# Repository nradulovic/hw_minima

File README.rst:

.. contents:: Table of Contents
   :depth: 3

Introduction
============

This document shall describe rationales used to design and build audio 
power amplifier using LM1875 integrated circuit.

Architecture
============

The amplifier architecture consists of the following sections:

* Input circuit
* Power amplifier
* Power supply

All sections are located on separate PCB boards.

.. image:: images/pcb_from_top.png

.. image:: images/pcb_render_corner.png

.. image:: images/pcb_render_from_top.png

Input circuit 
==================================

The input circuit contains:

* Input EMI suppression

Input EMI suppression
---------------------

To protect the input from EMI we will use the following Zobel network:

.. code::
          o Positive input or negative input
          |
          |
        ----- Czi
        -----
          |
          |
         +-+  Rzi
         | |
         | |
         +-+
          |
         === Ground

For most input cables characteristic impedance falls in range between
50 and 100ohm impedance and we are using the 75ohm as the middle value. The
resistor Rzi is ``Rzi=75ohm`` and the capacitor Czi is ``Czi=220pF``.
This network should be placed right at the input connector, not on the
main amplifier PCB.

Also, a 100n X7R capacitor shall be placed between SGND and chassis right at the
input connector. This capacitor will shunt radio and other interfirence signal
into the Chassis Ground potential.

Power amplifier
===============

* Input low pass filter
* The ground loop breaker resistor
* Output EMI suppression

Input low pass filter
---------------------

For input filter we choose the frequency between 300kHz and 400kHz.

.. code::

        +---+ Rlp1    +---+ Rlp2
    0---+   +----+----+   +---+---o Toward Amplifier IC block
        +---+    |    +---+   |
               ----- Clp1   ----- Clp2
               -----        -----
                 |            |
                === Ground   === Ground

Using the 2nd order CR low-pass filter calculator at URL:
*http://sim.okawa-denshi.jp/en/CRCRtool.php* we arrive at:

.. math::

    Rlp1 = 100 Ohm, Rlp2 = 100 Ohm

    Clp1 = 220pF,   Clp2 = 2.2nF

    fp1 = 352kHz

    fp2 = 14MHz

For more details please refer to: http://www.johnhearfield.com/RC/RC4.htm

The ground loop breaker resistor
--------------------------------

A ground loop breaker resistor is located between SGND and GNDPWR grounds. The
value of this resistor should be around 10 ohms.

Output EMI suppression
----------------------

Output network consists of upstream and downstream Zobel Network and of output
coil (``Ld``) with parallel, damping resistor (``Rd``). Upstream Zobel network 
provides a low-inductance load for the output stage at very high frequencies 
and allows high-frequency currents to circulate local to the output stage. The 
downstream Zobel network provides a good resistive termination right at the 
speaker terminals at high frequencies, helping to reduce RFI ingress and damp
resonances with, or reflections from, the speaker cables.
The output circuit is the following:

.. code::

    Ld
             xxx
        +---x   x   x---+
        |        xxx    |
        |               |
        |   +-------+   |
    o---+---|       |---+---o
    Vout    +-------+   |   Vspeaker
        Rd              |
                      ----- Cz2 = 100nF
                      -----
                        |
                        |
                       +-+  Rz1 = 10 Ohm
                       | |
                       | |
                       +-+
                        |
                       ===

The output coil ``Ld`` provides high frequency isolation of output load from 
output stage of LM1875. The inductance value should be between 2uH up to 5uH. 
Output shunt resistor should be between 2 Ohm and 5 Ohms. See 
*Douglas Self - Audio Power Amplifier Design Handbook, 3rd Ed., Output networks, 
chapter 7* for effect on power amplifier transfer function.

Power dissipation
-----------------

**NOTE:**

* Maximum power dissipation should be around 25W per IC package for LM1875.

Fortunately, with music signals the power dissipation should be lower. 
Effective power of music signal is about 2 to 10 times as smaller than 
effective power of sinusoid signal. The power transformer is 200VA, meaning 
that each channel gets 100VA of power. Since the maximum output power at 8ohms 
is approximately 50W we get that the transformer supports crest factor of 4 
(see: 
*https://www.neurochrome.com/taming-the-lm3886-chip-amplifier/power-supply-design*).

Gain value
----------

For this power amplifier we are using non-inverting topology for simplicity
reasons. If you would like to have less distortion then LM1875 should be used
in inverting configuration.

The equivalent gain circuit resistance needs to stay below 600ohms. This is so
because all noise measurements in data-sheet were done with 600ohms or 0ohms.

Using low feedback gain is preferred for several reasons:

* there is more loop gain available to reduce the distortion
* reduced output noise
* lower offset at output

Nominal gain is:

.. math::

    G=-Rf/Rg+1

Using E24 series of resistors:

+-----------+-----------+---------+
| Rf [Ohm]  | Rg [kOhm] | G [V/V] |
+-----------+-----------+---------+
| 510       |  7.5      | 15.7    |
+-----------+-----------+---------+
| *510*     |  *8.2*    | *17.0*  |
+-----------+-----------+---------+
| 510       |  9.1      | 18.8    |
+-----------+-----------+---------+
| 510       | 10.0      | 20.6    |
+-----------+-----------+---------+
| 510       | 11.0      | 22.5    |
+-----------+-----------+---------+

Using E48 series of resistors:

+-----------+-----------+---------+
| Rf [Ohm]  | Rg [kOhm] | G [V/V] |
+-----------+-----------+---------+
| 511       |  7.50     | 15.7    |
+-----------+-----------+---------+
| 511       |  7.87     | 16.4    |
+-----------+-----------+---------+
| *511*     |  *8.25*   | *17.1*  |
+-----------+-----------+---------+
| 511       |  8.66     | 17.9    |
+-----------+-----------+---------+
| 511       |  9.09     | 18.8    |
+-----------+-----------+---------+
| 511       |  9.53     | 19.6    |
+-----------+-----------+---------+
| 511       | 10.00     | 20.6    |
+-----------+-----------+---------+
| 511       | 10.50     | 21.5    |
+-----------+-----------+---------+
| 511       | 11.00     | 22.5    |
+-----------+-----------+---------+
| 499       |  7.50     | 16.0    |
+-----------+-----------+---------+

Chosen values for E24 series:

* Rf = 7.5kOhm
* Rg = 510 Ohm
    
Chosen values for E48 series:

* Rf = 7.5kOhm
* Rg = 499 Ohm
 
Frequency compensation
----------------------

The LM1875 is modeled in the following way:

* ``Aol``, typical open loop gain at DC.
* ``Fp1``, dominant pole.
* ``Fp2``, a pole which probably originates from output stage.
* ``Fp3``, pole which probably originates from input or intermediate stages.
* ``Fp4 Hz``, pole which probably originates from input or intermediate stages.
* ``Rops``, open loop output stage impedance. The OPS open loop impedance is 
  unusually low because the LM1875 uses output inclusive Miller compensation
  which can be observed on the equivalent schematic in the data-sheet.

+-----------+-----------+-----------+-----------+-----------+-----------+-----------+
| Chip      | Aol [dB]  | Fp1 [Hz]  | Fp2 [Hz]  | Fp3 [Hz]  | Fp4 [Hz]  | Rops [Ohm]|
+-----------+-----------+-----------+-----------+-----------+-----------+-----------+
| LM1875    | 90        | 15        | 1.5e6     | 8e6       | 9e6       | 500e-3    |
+-----------+-----------+-----------+-----------+-----------+-----------+-----------+

Lead compensation
`````````````````

Equivalent feedback network with lead compensation circuit::

          + Vout
          |
          *------+
          |      |
         +-+ Rf  |
         | |   ----- Cf=Cl (+Csi, see Input pin capacitance compensation)
         | |   -----
         +-+     |
   Vf     |      |
    +-----*------+
          |
         +-+ Rg
         | |
         | |
         +-+
          |
          + Input

Resistors `Rf` and `Rg` are part of feedback network. Capacitor `Cf` is the
compensation capacitor. The transfer function of this network is given as:

.. math::

    Vf(s)=I(s)*Rg

    Vout(s)=I(s)*(Rf||Cl + Rg)=I(s)*(Rf/(1+s*Rf*Cl)+Rg)

    H(s)=Vf(s)/Vout(s)=(Rg/(Rf+Rg))*((1+s*Rf*Cl)/(1+s*Re*Cl))

Zero: 

.. math::

    wz=1/(Rf*Cl)

Pole: 

.. math::

    wp=1/(Re*Cl)

Where:

.. math::

    Re=Rf||Rg=Rf*Rg/(Rf+Rg)

With this compensation we want to compensate for LM3886 ``fp2`` pole. Although
the ``fp2`` pole has a high value of it still has quite the effect on the gain 
phase near unity gain bandwidth (UGBW) value. To compensate for ``fp2``
pole we can use ``wz`` equation above. 

For LM1875 we would get:

.. math::
    
    Rf = 7.5kOhm
    
    fp2 = 1.5e6 Hz
    
    Cl=1/(2*pi*Rf*fp2)=14.1pF
    
Outcome:

* By using this compensation we improve the loop gain phase around UGBW point
  and at higher frequencies.
* The ``Cf`` in this compensation is known to reduce the closed loop
  bandwidth. Since the ``Cf`` value is so small the impact to closed loop
  bandwidth should be minimal.

Input pin capacitance compensation
``````````````````````````````````

Input pins have the following parasitic capacitances associated:

* Cdiff
* Cm
* Cstray

The LM1875 data-sheet does not specify any parameter regarding parasitic
input capacitances. Voltage feedback OPAMPS usually have both differential and
common-mode input impedances specified. In the absence of any information, it
is safe to use the model given in the next figure:

.. code::

                   +----+ Zdiff
    +input o---+---|    |---+---o -input
               |   +----+   |
               |            |
              +-+ Zcm1     +-+ Zcm2
              | |          | |
              | |          | |
              +-+          +-+
               |            |
              ===          ===

We can use a rough estimation of values based on experience on using other 
audio BJT OPAMPS, and typical values are around ``Cdiff=5pF``, ``Cm=4pF`` 
and ``Cstray=3pF``. All three equivalent capacitors are tied in parallel, 
so the total input capacitance becomes:

.. math::

    Cinput = Cdiff+Cm+Cstray=5pF+5pF+3pF=12pF
    
To mitigate this capacitance we can add capacitance `Csi` parallel to `Rf` 
resistor. To compensate for this the following equation is applied:

.. math::

    Rf*Csi=Rg*Cinput
    
    Csi=Cinput*Rg/Rf=0.8pF
    
Since we are already using lead compensation we just add this value to existing
`Cl` capacitor.

Also, note that LM1875 model has tree more additional poles:

* ``Fp2``, pole which probably originates from input or intermediate 
  stages.
* ``Fp3``, pole which probably originates from input or intermediate 
  stages.
* A pole from ``Rops``, open loop output stage impedance which in conjunction 
  with output Zobel and connected load forms another high frequency pole.
   
Although all above poles are very high in frequency they still have their
impact on lower frequency part of transfer function and reduce a few degrees of
phase margin at UGBW point (approx. at 500kHz). Because of these poles we can
freely put a bit bigger `Cf` capacitor value in the feedback network. Rough
estimation is to put additional 1-3pF.

.. math::

	Cadd = 2pF

For LM1875 we get:

.. math::

    Cf=Cl+Csi+Cadd=14.1+0.8+2pF=16.9pF
    
Since the closest, standard values of capacitors are 15pF and 18pF, we choose
the 15pF as the final value for `Cl` capacitor:

.. math::

    Cf=15pF 

Power supply
============

Before rectifier diodes a snubber RC circuit should be placed to decrease diode
switching impulse. Recommended values are ``Rsn = 1 Ohm``, ``Csn = 470nF``::

          o Vsupply
          |
          |
        ----- Csn = 470nF
        -----
          |
          |
         +-+  Rsn = 1 Ohm
         | |
         | |
         +-+
          |
         === Ground

This snubber may be placed near the IC power supply lines, too.

Using stabilized power supplies, for example by using LT1083 regulator is only
meaningful at lower output powers. The regulation becomes really expensive when
used in high power amplifiers. Regulated power supplies are OK when used up to
powers of 20W-30W @ 8 Ohm.

**NOTE:**

* On case chassis there should be a safety ground screw just near at the input
  220V socket.

Transformer specification for LM1875 amplifier is the following:

* ``S=80VA``, power rating.
* ``Usn1=18Veff``, first secondary nominal voltage.
* ``Usn2=18Veff``, second secondary nominal voltage.
* ``k=10%``, regulation.

Secondary internal resistance is:

.. math::

    Usu=Usn1*(1+(k/100))
    
    Isn=S/(Usn1+Usn2)
    
    Ri=(Usn1-Usu)/Isn
    
Using values from above we get:

.. math:: 
    
    Usu=18*(1+(10/100))=19.8Veff
    
    Isn=2.2Aeff

    Ri=810mOhm
    
The power supply section is using single banks of 10mF capacitors with 0.22Ohm
resistor in series between bridge rectifier and smoothing capacitors.

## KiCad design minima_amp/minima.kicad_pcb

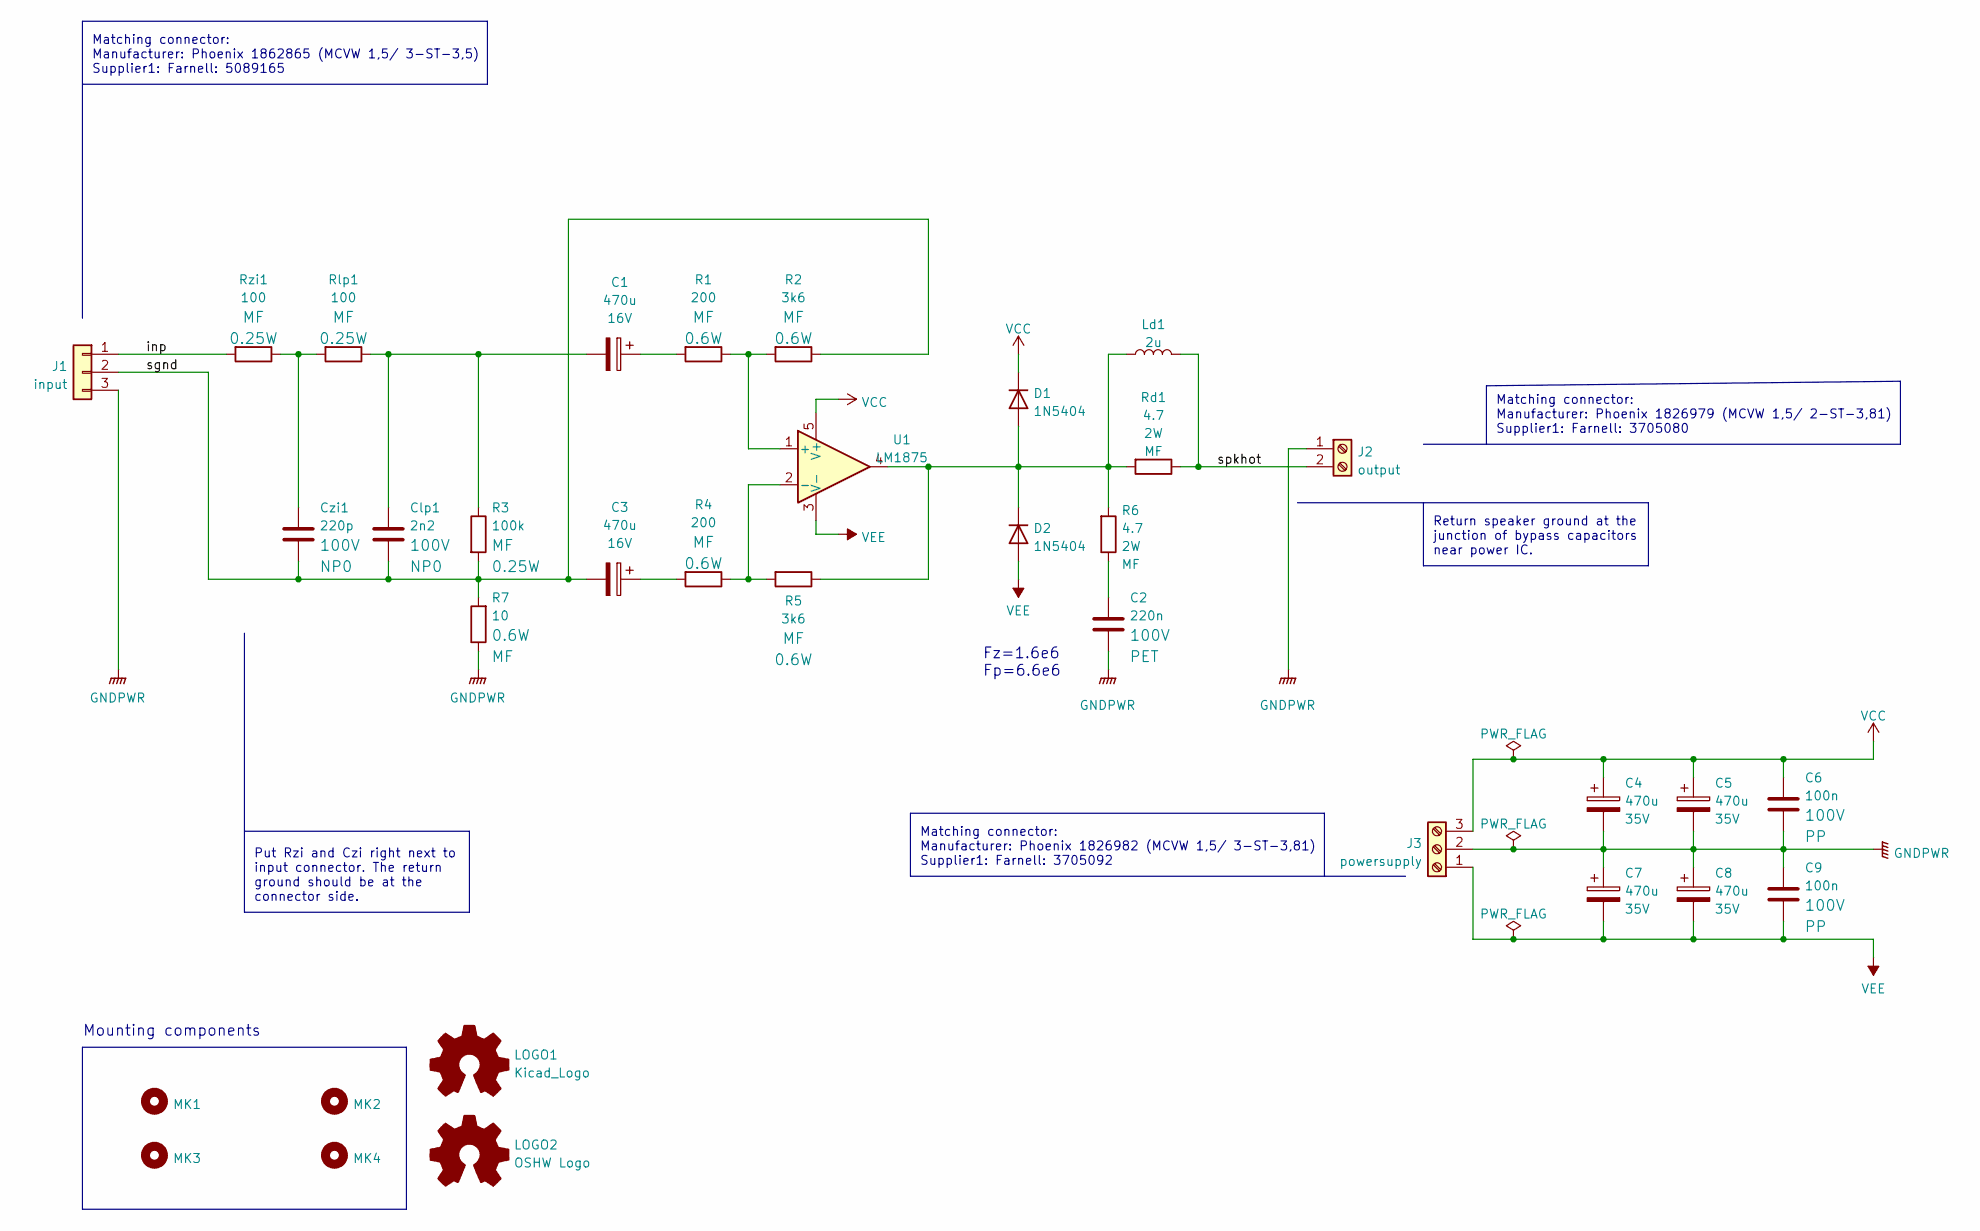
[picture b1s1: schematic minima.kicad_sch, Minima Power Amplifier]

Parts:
C1, C3: 470u; CP_Radial_D8.0mm_P3.50mm; Voltage 16V
C2: 220n; C_Rect_L7.0mm_W3.5mm_P5.00mm; Voltage 100V
C4, C5, C7, C8: 470u; CP_Radial_D10.0mm_P5.00mm; Voltage 35V
C6, C9: 100n; C_Rect_L7.0mm_W3.5mm_P5.00mm; Voltage 100V
Clp1: 2n2; C_Disc_D4.3mm_W1.9mm_P5.00mm; Voltage 100V
Czi1: 220p; C_Disc_D4.3mm_W1.9mm_P5.00mm; Voltage 100V
D1, D2: 1N5404; D_DO-201AD_P15.24mm_Horizontal
J1: input; PhoenixContact_MCV_1,5_3-G-3.5_1x03_P3.50mm_Vertical
J2: output; PhoenixContact_MCV_1,5_2-G-3.81_1x02_P3.81mm_Vertical
J3: powersupply; PhoenixContact_MCV_1,5_3-G-3.81_1x03_P3.81mm_Vertical
LOGO1: Kicad_Logo; KiCad-Logo_5mm_Copper
LOGO2: OSHW Logo; OSHW-Logo2_7.3x6mm_SilkScreen
Ld1: 2u; L_Axial_L12.0mm_D5.0mm_P15.24mm_Horizontal_Fastron_MISC
MK1, MK2, MK3, MK4: Mounting_Hole; MountingHole_3.2mm_M3_ISO7380_Pad
R1, R4: 200; R_Axial_DIN0207_L6.3mm_D2.5mm_P10.16mm_Horizontal
R2, R5: 3k6; R_Axial_DIN0207_L6.3mm_D2.5mm_P10.16mm_Horizontal
R3: 100k; R_Axial_DIN0207_L6.3mm_D2.5mm_P10.16mm_Horizontal
R6: 4.7; R_Axial_DIN0411_L9.9mm_D3.6mm_P15.24mm_Horizontal
R7: 10; R_Axial_DIN0207_L6.3mm_D2.5mm_P10.16mm_Horizontal
Rd1: 4.7; R_Axial_DIN0411_L9.9mm_D3.6mm_P15.24mm_Horizontal
Rlp1: 100; R_Axial_DIN0207_L6.3mm_D2.5mm_P10.16mm_Horizontal
Rzi1: 100; R_Axial_DIN0207_L6.3mm_D2.5mm_P10.16mm_Horizontal
U1: LM1875; TO-220-5_P3.4x3.7mm_StaggerOdd_Lead3.8mm_Vertical

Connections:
/inp: J1.1, Rzi1.2
/sgnd: C3.2, Clp1.2, Czi1.2, J1.2, R2.1, R3.2, R7.2
/spkhot: J2.2, Ld1.2, Rd1.1
GNDPWR: C2.2, C4.2, C5.2, C6.2, C7.1, C8.1, C9.1, J1.3, J2.1, J3.2, R7.1
unnamed: C1.1, R1.2
unnamed: C1.2, Clp1.1, R3.1, Rlp1.1
unnamed: C2.1, R6.1
unnamed: C3.1, R4.2
unnamed: Czi1.1, Rlp1.2, Rzi1.1
unnamed: D1.2 (A), D2.1 (K), Ld1.1, R5.1, R6.2, Rd1.2, U1.4
unnamed: R1.1, R2.2, U1.1 (+)
unnamed: R4.1, R5.2, U1.2 (-)
VCC: C4.1, C5.1, C6.1, D1.1 (K), J3.3, U1.5 (V+)
VEE: C7.2, C8.2, C9.2, D2.2 (A), J3.1, U1.3 (V-)

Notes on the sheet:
Matching connector: Manufacturer: Phoenix 1862865 (MCVW 1,5/ 3-ST-3,5) Supplier1: Farnell: 5089165
Put Rzi and Czi right next to input connector. The return ground should be at the connector side.
Return speaker ground at the junction of bypass capacitors near power IC.
Mounting components
Fz=1.6e6 Fp=6.6e6
Matching connector: Manufacturer: Phoenix 1826979 (MCVW 1,5/ 2-ST-3,81) Supplier1: Farnell: 3705080
Matching connector: Manufacturer: Phoenix 1826982 (MCVW 1,5/ 3-ST-3,81) Supplier1: Farnell: 3705092

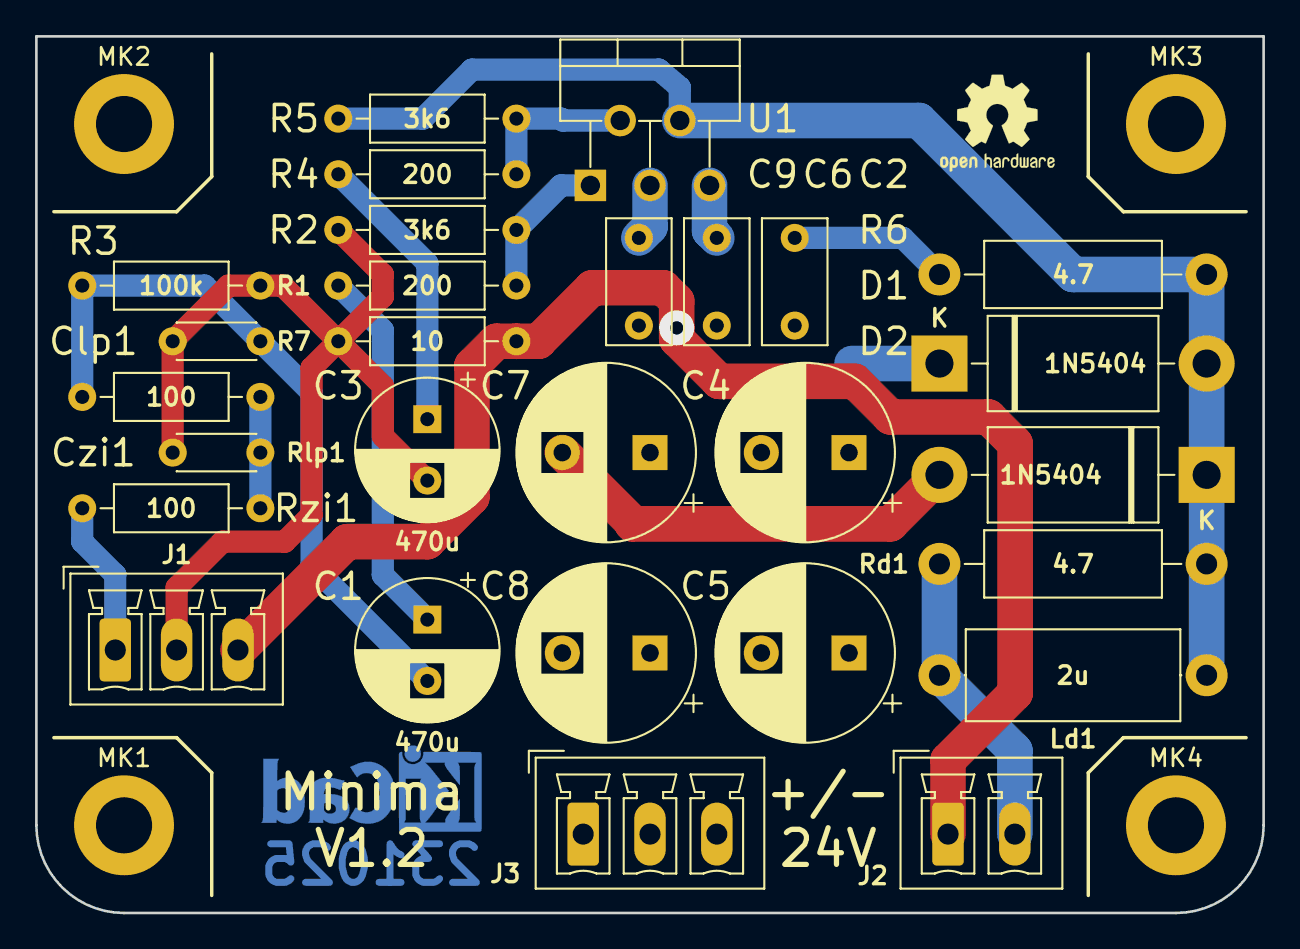
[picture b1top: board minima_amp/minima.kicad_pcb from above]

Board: 2 copper layers, 70.0 x 50.0 mm, 34 parts (1 on the bottom side), 14 nets.

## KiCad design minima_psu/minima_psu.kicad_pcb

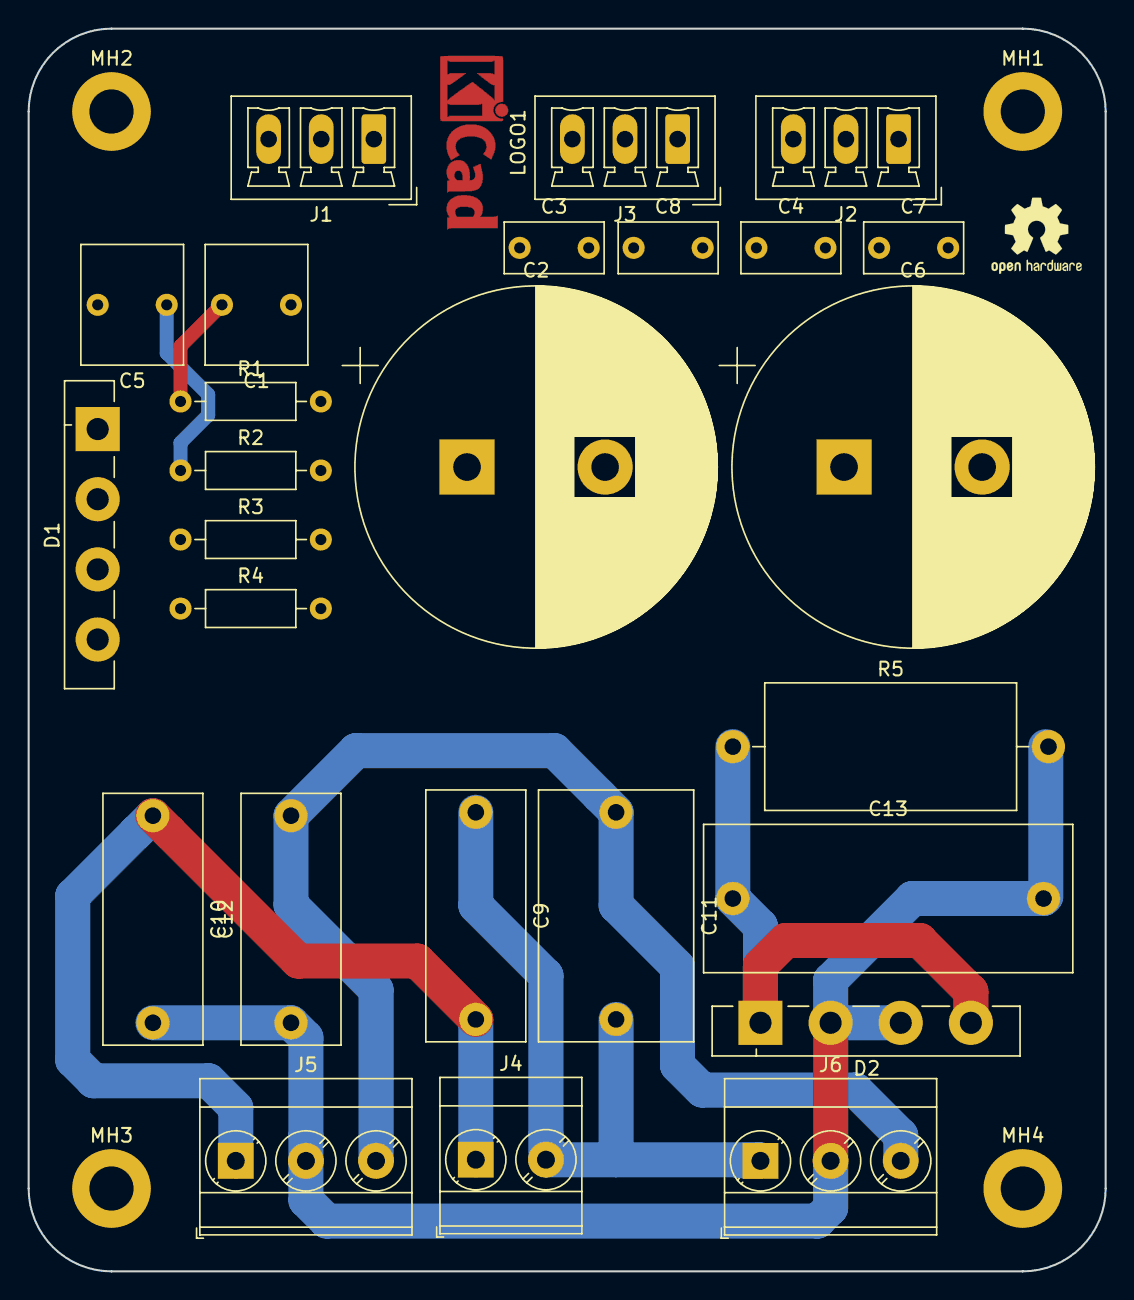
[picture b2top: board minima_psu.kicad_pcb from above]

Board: 2 copper layers, 78.0 x 90.0 mm, 32 parts (0 on the bottom side), 11 nets.

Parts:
C1, C5: 470n; C_Rect_L7.2mm_W8.5mm_P5.00mm_FKP2_FKP2_MKS2_MKP2
C2, C6: 6m8; CP_Radial_D26.0mm_P10.00mm_SnapIn
C3, C4, C7, C8: 100n; C_Rect_L7.0mm_W3.5mm_P5.00mm
C9, C10, C12: 22n; C_Rect_L18.0mm_W7.0mm_P15.00mm_FKS3_FKP3
C11: 470n; C_Rect_L18.0mm_W11.0mm_P15.00mm_FKS3_FKP3
C13: 100n; C_Rect_L26.5mm_W10.5mm_P22.50mm_MKS4
D1, D2: GBU2508F; Diode_Bridge_Vishay_GBU
J1: power; PhoenixContact_MCV_1,5_3-G-3.81_1x03_P3.81mm_Vertical
J2, J3: psupply; PhoenixContact_MCV_1,5_3-G-3.81_1x03_P3.81mm_Vertical
J4: switch; TerminalBlock_Phoenix_MKDS-3-2-5.08_1x02_P5.08mm_Horizontal
J5: ac_in; TerminalBlock_Phoenix_MKDS-3-3-5.08_1x03_P5.08mm_Horizontal
J6: transformer; TerminalBlock_Phoenix_MKDS-3-3-5.08_1x03_P5.08mm_Horizontal
LOGO1: Kicad_Logo; KiCad-Logo_5mm_Copper
LOGO2: Kicad_Logo; OSHW-Logo2_7.3x6mm_SilkScreen
MH1, MH2, MH3, MH4: MountingHole; MountingHole_3.2mm_M3_ISO7380_Pad
R1, R2: 1; R_Axial_DIN0207_L6.3mm_D2.5mm_P10.16mm_Horizontal
R3, R4: 10k; R_Axial_DIN0207_L6.3mm_D2.5mm_P10.16mm_Horizontal
R5: 10; R_Axial_DIN0918_L18.0mm_D9.0mm_P22.86mm_Horizontal

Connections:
/ac_l: C9.2, C10.1, J4.1, J5.1
/ac_n: C11.1, C12.2, J5.3, J6.3
/acs_n: C5.2, D1.2, J1.3
/acs_p: C1.1, D1.3, J1.1
/vcc: C2.1, C3.1, C4.1, D1.1, J2.1, J3.1, R3.1
/vee: C6.2, C7.2, C8.2, D1.4, J2.3, J3.3, R4.1
Earth_Protective: C10.2, C12.1, C13.2, D2.2, D2.3, J5.2, J6.2, R5.2
GNDPWR: C2.2, C3.2, C4.2, C6.1, C7.1, C8.1, C13.1, D2.1, D2.4, J1.2, J2.2, J3.2, R1.2, R2.2, R3.2, R4.2, R5.1
unnamed: C1.2, R1.1
unnamed: C5.1, R2.1
unnamed: C9.1, C11.2, J4.2, J6.1

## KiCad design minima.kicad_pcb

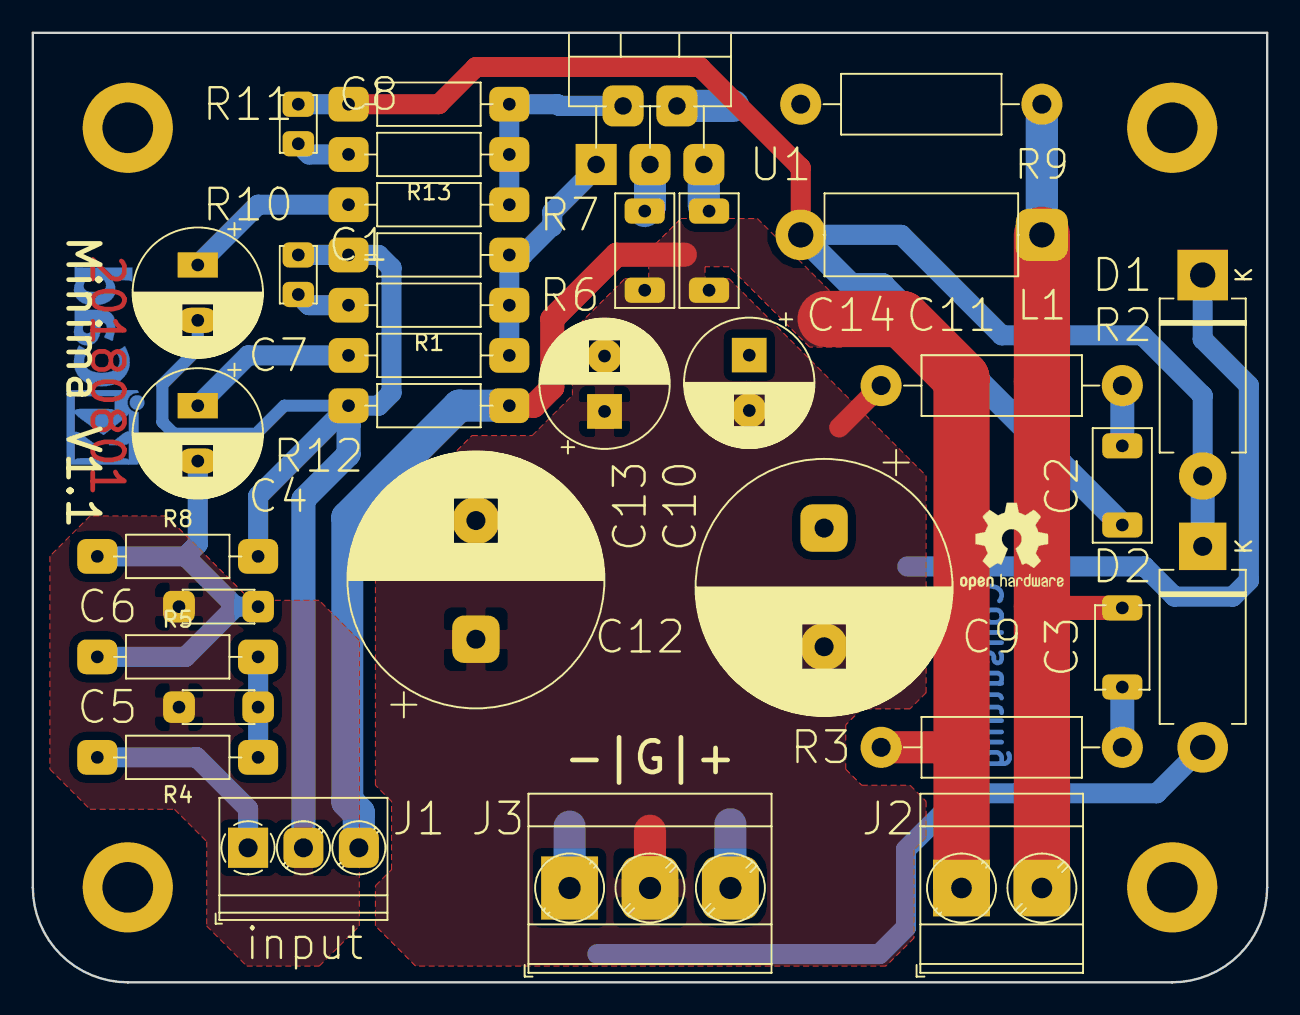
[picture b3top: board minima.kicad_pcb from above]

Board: 2 copper layers, 78.0 x 60.0 mm, 40 parts (1 on the bottom side), 17 nets.

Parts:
C1, C8: 15p; C_Disc_D3.4mm_W2.1mm_P2.50mm
C2: 220n; C_Rect_L7.0mm_W3.5mm_P5.00mm
C3: 100n; C_Disc_D5.1mm_W3.2mm_P5.00mm
C4, C7: 470u; CP_Radial_D8.0mm_P3.50mm
C5: 220p; C_Disc_D4.3mm_W1.9mm_P5.00mm
C6: 2n2; C_Disc_D4.3mm_W1.9mm_P5.00mm
C9, C12: 2m2; CP_Radial_D16.0mm_P7.50mm
C10, C13: 100u; CP_Radial_D8.0mm_P3.50mm
C11, C14: 100n; C_Rect_L7.0mm_W3.5mm_P5.00mm
D1, D2: 1N5404; D_DO-201AD_P12.70mm_Horizontal
J1: input; TerminalBlock_Phoenix_PT-1,5-3-3.5-H_1x03_P3.50mm_Horizontal
J2: output; TerminalBlock_Phoenix_MKDS-3-2-5.08_1x02_P5.08mm_Horizontal
J3: powersupply; TerminalBlock_Phoenix_MKDS-3-3-5.08_1x03_P5.08mm_Horizontal
L1: 2u; L_Axial_L12.0mm_D5.0mm_P15.24mm_Horizontal_Fastron_MISC
LOGO1: Kicad_Logo; KiCad-Logo_5mm_Copper
LOGO2: OSHW Logo; OSHW-Logo2_7.3x6mm_SilkScreen
MK1, MK2, MK3, MK4: Mounting_Hole; MountingHole_3.2mm_M3_ISO7380_Pad
R1, R13: 1k6; R_Axial_DIN0207_L6.3mm_D2.5mm_P10.16mm_Horizontal
R2, R9: 4.7; R_Axial_DIN0411_L9.9mm_D3.6mm_P15.24mm_Horizontal
R3: 10; R_Axial_DIN0411_L9.9mm_D3.6mm_P15.24mm_Horizontal
R4, R5: 100; R_Axial_DIN0207_L6.3mm_D2.5mm_P10.16mm_Horizontal
R6, R10: 499; R_Axial_DIN0207_L6.3mm_D2.5mm_P10.16mm_Horizontal
R7, R11: 7k5; R_Axial_DIN0207_L6.3mm_D2.5mm_P10.16mm_Horizontal
R8: 100k; R_Axial_DIN0207_L6.3mm_D2.5mm_P10.16mm_Horizontal
R12: 10; R_Axial_DIN0207_L6.3mm_D2.5mm_P10.16mm_Horizontal
U1: LM1875; TO-220-5_P3.4x3.7mm_StaggerOdd_Lead3.8mm_Vertical

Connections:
/inp: J1.1, R4.2
/sgnd: C1.1, C5.2, C6.2, C7.2, J1.2, R7.1, R8.2, R12.2
/spkhot: C3.2, J2.2, L1.2, R9.1
GNDPWR: C9.2, C10.2, C11.2, C12.1, C13.1, C14.1, J1.3, J2.1, J3.2, R2.1, R3.1, R12.1
unnamed: C1.2, R1.2
unnamed: C2.1, R2.2
unnamed: C2.2, C8.1, D1.2, D2.1, L1.1, R9.2, R11.1, U1.4
unnamed: C3.1, R3.2
unnamed: C4.1, R6.2
unnamed: C4.2, C6.1, R5.1, R8.1
unnamed: C5.1, R4.1, R5.2
unnamed: C7.1, R10.2
unnamed: C8.2, R13.2
unnamed: R1.1, R6.1, R7.2, U1.1
unnamed: R10.1, R11.2, R13.1, U1.2
VCC: C9.1, C10.1, C11.1, D1.1, J3.3, U1.5
VEE: C12.2, C13.2, C14.2, D2.2, J3.1, U1.3

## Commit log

2018-05-01 The board shall now support single channel only.
2018-07-31 Switched to Kicad 5.0
2018-07-31 Updated regarding v5.0
    Still updateing regarding transition to v5.0
2018-07-31 Version 1.0b
2018-08-02 Release Version 1.0
2018-08-05 Releasing version with distant psu caps.
2018-08-06 Added README.rst description file.
2018-08-06 Relase v1.0
    Corrected a few things on the PCB.
2018-08-06 Revised some pad holes.
2018-08-06 Release version v1.1
2018-08-07 Switching to single sch sheet 1
2018-08-07 Removed sheets
2018-08-07 Wider pads and some final touches to silkscreen.
2018-08-10 Started work on Minima PSU.
2018-08-17 Pad update and LOGO fix
    Updated sizes of pads. Some are bigger while keeping the necessary separations.
2018-08-20 Added hole dimensions to PCB
    Added mounting hole space dimensions.
2018-08-28 Fixed REAL TIME CONSULTING alignment
2018-08-28 Updated notes about upcoming Monitor module.
2018-08-28 Started work on PSU description.
2018-08-28 Formatting fixes.
2018-09-03 Added information about highest components.
2018-09-03 Reworked ground pour aroung SGND input.
2018-09-10 Added mechanical components
2018-09-11 Added SN and Date fields on PCB
2018-12-07 Added spice simulation files.
2019-01-22 Minor PCB adjustements
2019-01-22 Updated README and gitignore.
2019-01-22 Added 28pin PIC18 column in the pin mapping table.
2019-01-22 Added SPICE files to minima_amp
2019-01-22 Update README format
2019-01-23 Using designators as specified in README.rst
2019-01-23 Redo the formatting of text and minor corrections in README.rst
2019-01-24 Added small intro text.
2019-01-26 WIP: Layout of PCB.
2019-01-30 Added some nice pictures
2019-01-30 Fixed formatting errors
2019-01-30 Just update the titles
2019-01-30 Using Pluggable Terminal Block
2019-01-31 Updated README.rst formatting
2019-01-31 Updated images
2019-01-31 Added comments about connectors
2019-01-31 Release of v1.1
2019-02-04 WIP: Component routing & placement
2019-02-04 Added comment about matching connector
2021-08-31 chore: update README contents to match actual project implementation
2021-08-31 fix: proper README title size
2022-02-14 feat: simpler schematic
2023-09-26 Release of Version 1.2
